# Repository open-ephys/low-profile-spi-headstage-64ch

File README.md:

# Low-profile SPI Headstage with 64 ephys channels

## Accelerometer orientation

## Licensing

The designs, documentation, and photos available in this repository are free: you can redistribute it and/or modify it under the terms of the used license.
Check file named LICENSE.

Copyright Filipe Carvalho and Jonathan Newman 2020-2022

<br />This work is licensed under a <a rel="license" href="http://creativecommons.org/licenses/by-nc-sa/3.0/igo/">Creative Commons Attribution-NonCommercial-ShareAlike 3.0 IGO License</a>.

If your are interested in obtaining a license to sell this device, please contact info@open-ephys.org

[1]: https://docs.google.com/spreadsheets/d/1aobmmEzBDethzIlrm1eg0eYkBqlyX3s9WbA9KgRwVQI/edit?usp=sharing

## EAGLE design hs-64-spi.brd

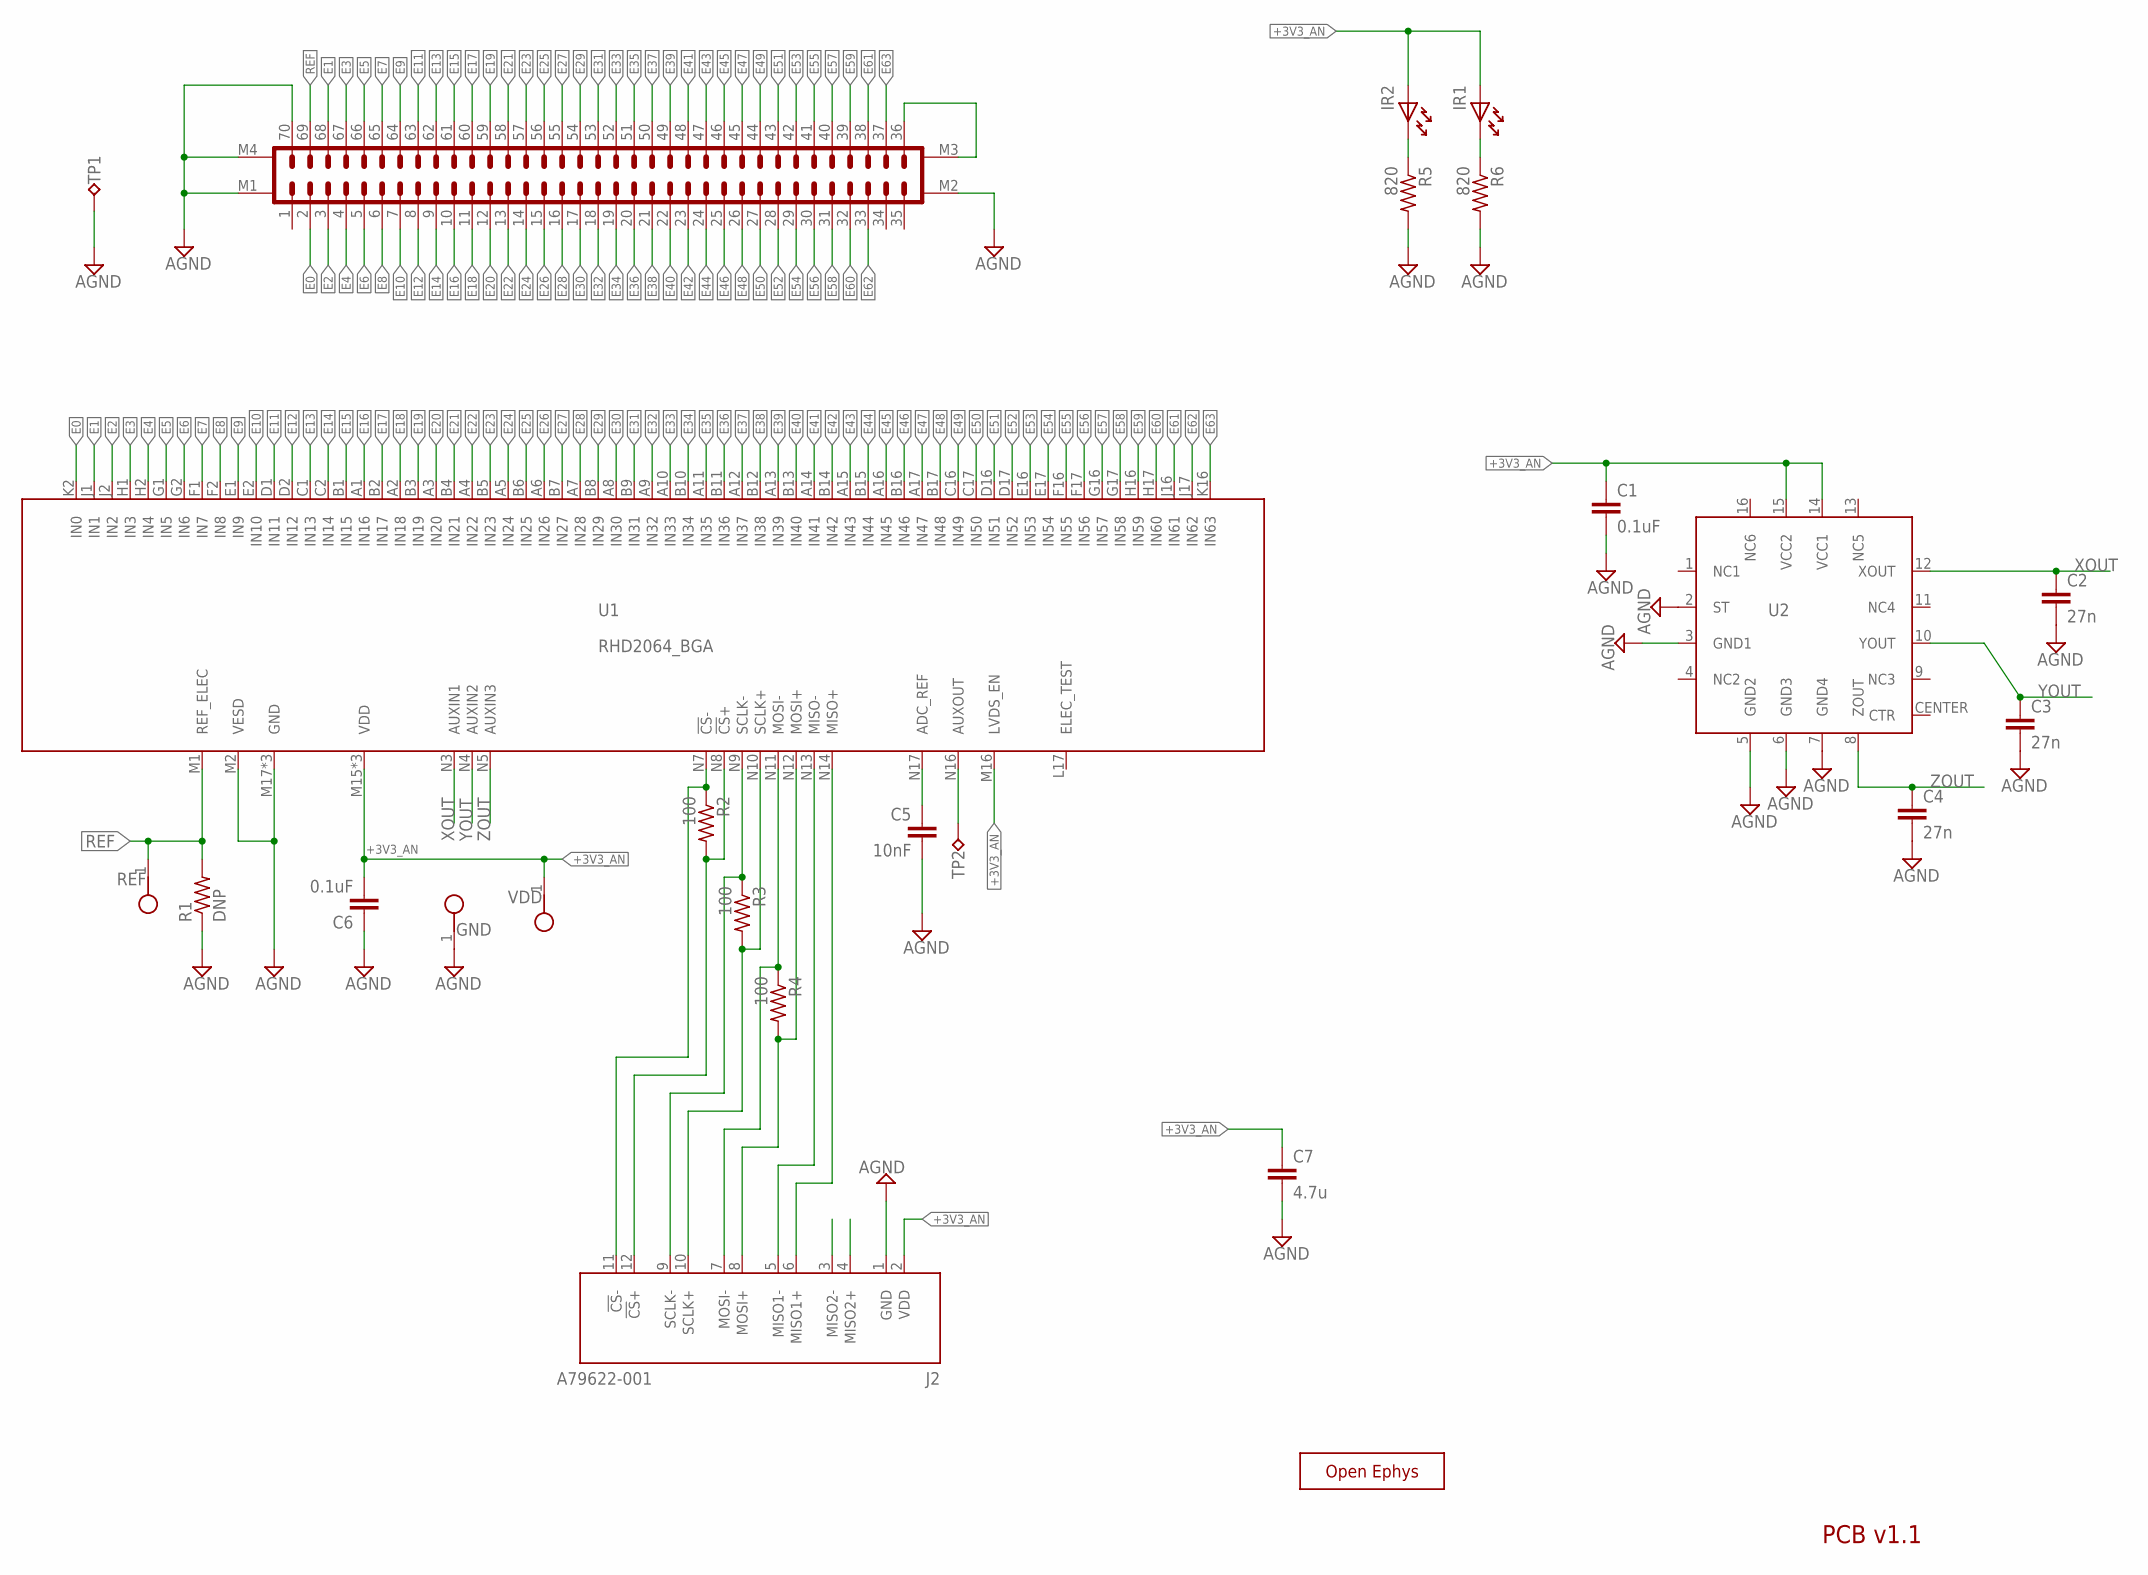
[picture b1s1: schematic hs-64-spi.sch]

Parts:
C1: 0.1uF; 0402
C2, C3, C4: 27n; 0402
C5: 10nF; 0402T; PARTNO GRM033R71E103KE14D
C6: 0.1uF; 0402T
C7: 4.7u; 0402
GND: TESTPOINT_SMALL
IR1, IR2: LEDHAND; LED_HAND
J1: DF40C-70DP-0.4V(51); DF40-70HEAD-LESS-SILK
J2: A79622-001
R1: DNP; 0603
R2, R3, R4: 100; 0402
R5, R6: 820; 0402
REF: TESTPOINT_SMALL
TP1, TP2: VCC; TP07R
U1: RHD2064_BGA; BGA104_0.5MM
U2: ADXL335_IDAX
VDD: TESTPOINT_SMALL
X: OE-LOGO_3.5X2.5; OE-LOGO-3.5X2.5

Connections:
+3V3_AN: C1.1, C6.2, C7.1, IR1.A, IR2.A, J2.2 (VDD), U1.M15 (VDD), U1.M16 (LVDS_EN), U1.N2 (VDD), U1.N15 (VDD), U2.14 (VCC1), U2.15 (VCC2), VDD.1
AGND: C1.2, C2.2, C3.2, C4.2, C5.2, C6.1, C7.2, GND.1, J1.70, J1.M1, J1.M2, J1.M4, J2.1 (GND), R1.1, R5.2, R6.2, TP1.TP, U1.M2 (VESD), U1.M17 (GND), U1.N1 (GND), U1.N6 (GND), U2.2 (ST), U2.3 (GND1), U2.5 (GND2), U2.6 (GND3), U2.7 (GND4)
E0: J1.2, U1.K2 (IN0)
E1: J1.68, U1.J1 (IN1)
E2: J1.3, U1.J2 (IN2)
E3: J1.67, U1.H1 (IN3)
E4: J1.4, U1.H2 (IN4)
E5: J1.66, U1.G1 (IN5)
E6: J1.5, U1.G2 (IN6)
E7: J1.65, U1.F1 (IN7)
E8: J1.6, U1.F2 (IN8)
E9: J1.64, U1.E1 (IN9)
E10: J1.7, U1.E2 (IN10)
E11: J1.63, U1.D1 (IN11)
E12: J1.8, U1.D2 (IN12)
E13: J1.62, U1.C1 (IN13)
E14: J1.9, U1.C2 (IN14)
E15: J1.61, U1.B1 (IN15)
E16: J1.10, U1.A1 (IN16)
E17: J1.60, U1.B2 (IN17)
E18: J1.11, U1.A2 (IN18)
E19: J1.59, U1.B3 (IN19)
E20: J1.12, U1.A3 (IN20)
E21: J1.58, U1.B4 (IN21)
E22: J1.13, U1.A4 (IN22)
E23: J1.57, U1.B5 (IN23)
E24: J1.14, U1.A5 (IN24)
E25: J1.56, U1.B6 (IN25)
E26: J1.15, U1.A6 (IN26)
E27: J1.55, U1.B7 (IN27)
E28: J1.16, U1.A7 (IN28)
E29: J1.54, U1.B8 (IN29)
E30: J1.17, U1.A8 (IN30)
E31: J1.53, U1.B9 (IN31)
E32: J1.18, U1.A9 (IN32)
E33: J1.52, U1.A10 (IN33)
E34: J1.19, U1.B10 (IN34)
E35: J1.51, U1.A11 (IN35)
E36: J1.20, U1.B11 (IN36)
E37: J1.50, U1.A12 (IN37)
E38: J1.21, U1.B12 (IN38)
E39: J1.49, U1.A13 (IN39)
E40: J1.22, U1.B13 (IN40)
E41: J1.48, U1.A14 (IN41)
E42: J1.23, U1.B14 (IN42)
E43: J1.47, U1.A15 (IN43)
E44: J1.24, U1.B15 (IN44)
E45: J1.46, U1.A16 (IN45)
E46: J1.25, U1.B16 (IN46)
E47: J1.45, U1.A17 (IN47)
E48: J1.26, U1.B17 (IN48)
E49: J1.44, U1.C16 (IN49)
E50: J1.27, U1.C17 (IN50)
E51: J1.43, U1.D16 (IN51)
E52: J1.28, U1.D17 (IN52)
E53: J1.42, U1.E16 (IN53)
E54: J1.29, U1.E17 (IN54)
E55: J1.41, U1.F16 (IN55)
E56: J1.30, U1.F17 (IN56)
E57: J1.40, U1.G16 (IN57)
E58: J1.31, U1.G17 (IN58)
E59: J1.39, U1.H16 (IN59)
E60: J1.32, U1.H17 (IN60)
E61: J1.38, U1.J16 (IN61)
E62: J1.33, U1.J17 (IN62)
E63: J1.37, U1.K16 (IN63)
unnamed: IR2.K, R5.1
unnamed: IR1.K, R6.1
unnamed: C5.1, U1.N17 (ADC_REF)
unnamed: TP2.TP, U1.N16 (AUXOUT)
REF: J1.69, R1.2, REF.1, U1.M1 (REF_ELEC)
RHD_CLK_N: J2.9 (SCLK-), R3.1, U1.N9 (SCLK-)
RHD_CLK_P: J2.10 (SCLK+), R3.2, U1.N10 (SCLK+)
RHD_CS_N: J2.11 (!CS!-), R2.1, U1.N7 (!CS!-)
RHD_CS_P: J2.12 (!CS!+), R2.2, U1.N8 (!CS!+)
RHD_MISO_N: J2.5 (MISO1-), U1.N13 (MISO-)
RHD_MISO_P: J2.6 (MISO1+), U1.N14 (MISO+)
RHD_MOSI_N: J2.7 (MOSI-), R4.1, U1.N11 (MOSI-)
RHD_MOSI_P: J2.8 (MOSI+), R4.2, U1.N12 (MOSI+)
VCOAX: J1.36, J1.M3
XOUT: C2.1, U1.N3 (AUXIN1), U2.12 (XOUT)
YOUT: C3.1, U1.N4 (AUXIN2), U2.10 (YOUT)
ZOUT: C4.1, U1.N5 (AUXIN3), U2.8 (ZOUT)

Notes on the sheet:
PCB v1.1

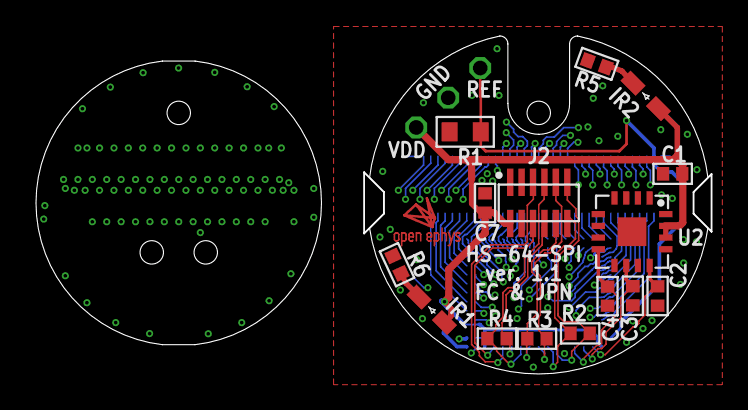
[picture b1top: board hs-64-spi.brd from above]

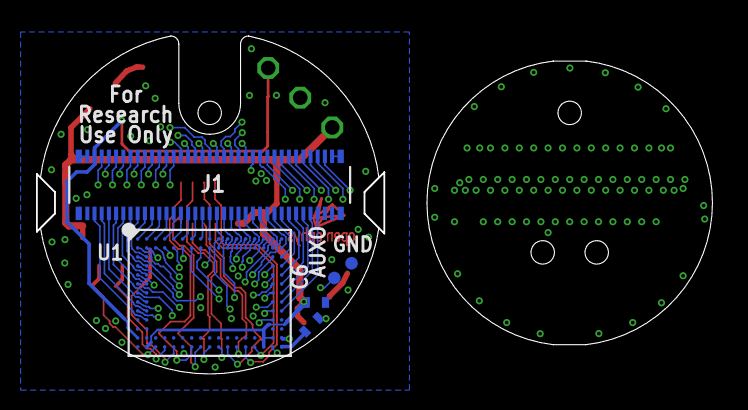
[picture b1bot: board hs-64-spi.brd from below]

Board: 4 copper layers, 37.5 x 18.7 mm, 25 parts (6 on the bottom side), 83 nets.

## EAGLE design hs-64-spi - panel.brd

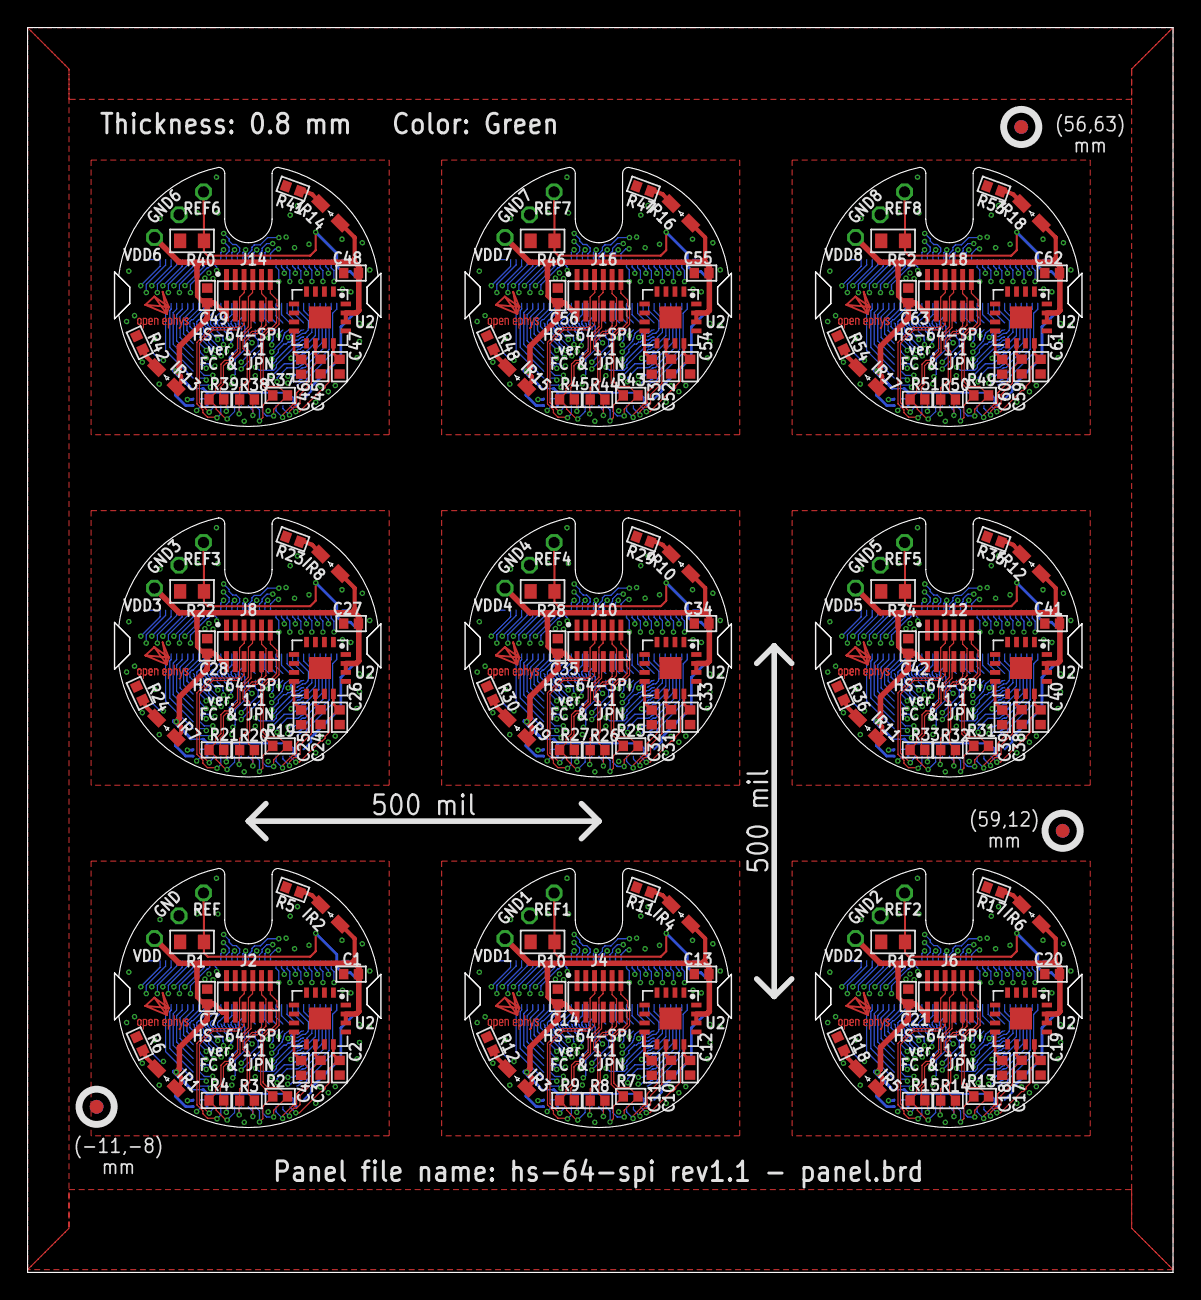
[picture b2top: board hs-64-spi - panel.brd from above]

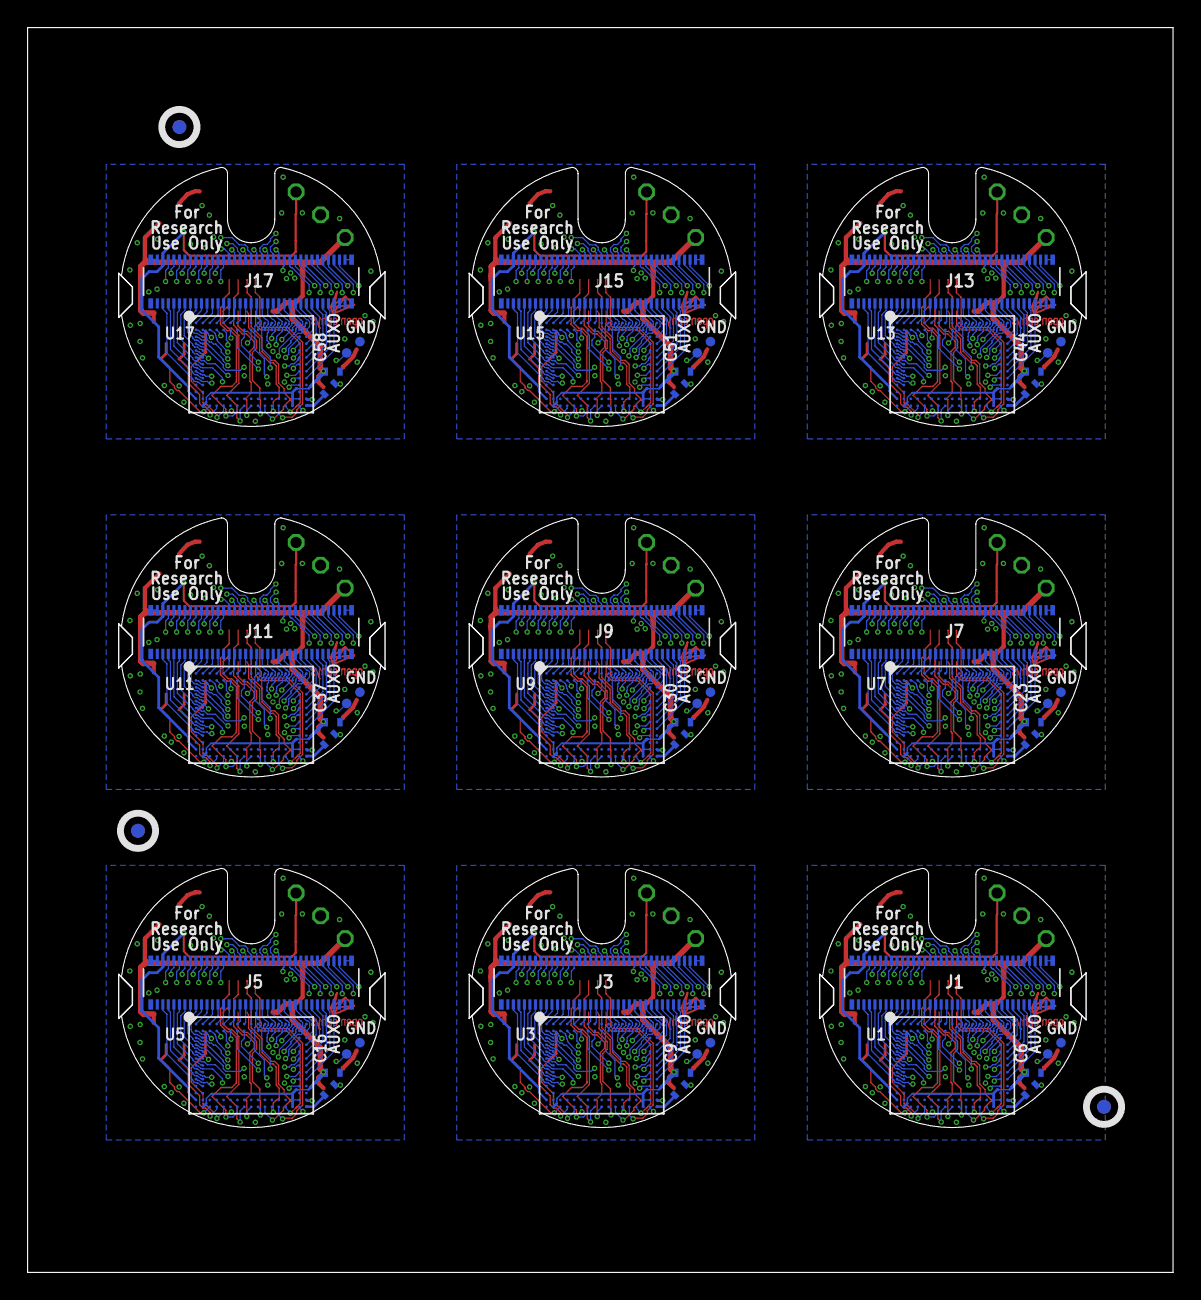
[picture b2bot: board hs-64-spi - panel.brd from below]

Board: 4 copper layers, 82.9 x 90.1 mm, 231 parts (57 on the bottom side), 747 nets.

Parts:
C1, C13, C20, C27, C34, C41, C48, C55, C62: 0.1uF; 0402
C2, C3, C4, C10, C11, C12, C17, C18, C19, C24, C25, C26, C31, C32, C33, C38, C39, C40, C45, C46, C47, C52, C53, C54, C59, C60, C61: 27n; 0402
C5, C8, C15, C22, C29, C36, C43, C50, C57: 10nF; 0402T
C6, C9, C16, C23, C30, C37, C44, C51, C58: 0.1uF; 0402T
C7, C14, C21, C28, C35, C42, C49, C56, C63: 1u; 0402
E$1, E$2, E$3, E$4, E$5, E$6: FIDUCIAL
GND, GND1, GND2, GND3, GND4, GND5, GND6, GND7, GND8: TESTPOINT_SMALL
IR1, IR2, IR3, IR4, IR5, IR6, IR7, IR8, IR9, IR10, IR11, IR12, IR13, IR14, IR15, IR16, IR17, IR18: LED_HAND
J1, J3, J5, J7, J9, J11, J13, J15, J17: DF40C-70DP-0.4V(51); DF40-70HEAD-LESS-SILK
J2, J4, J6, J8, J10, J12, J14, J16, J18: A79622-001
R1, R10, R16, R22, R28, R34, R40, R46, R52: DNP; 0603
R2, R3, R4, R7, R8, R9, R13, R14, R15, R19, R20, R21, R25, R26, R27, R31, R32, R33, R37, R38, R39, R43, R44, R45, R49, R50, R51: 100; 0402
R5, R6, R11, R12, R17, R18, R23, R24, R29, R30, R35, R36, R41, R42, R47, R48, R53, R54: 820; 0402
REF, REF1, REF2, REF3, REF4, REF5, REF6, REF7, REF8: TESTPOINT_SMALL
TP1, TP2, TP3, TP4, TP5, TP6, TP7, TP8, TP9, TP10, TP11, TP12, TP13, TP14, TP15, TP16, TP17, TP18: VCC; TP07R
U1, U3, U5, U7, U9, U11, U13, U15, U17: RHD2064_BGA; BGA104_0.5MM
U2, U4, U6, U8, U10, U12, U14, U16, U18: ADXL335_IDAX
VDD, VDD1, VDD2, VDD3, VDD4, VDD5, VDD6, VDD7, VDD8: TESTPOINT_SMALL
X, X1, X2, X3, X4, X5, X6, X7, X8: OE-LOGO_3.5X2.5; OE-LOGO-3.5X2.5

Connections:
+3V3_AN: C1.1, C6.2, C7.1, IR1.A, IR2.A, J2.2, U1.M15, U1.M16, U1.N2, U1.N15, U2.14, U2.15, VDD.1
+3V3_AN1: C9.2, C13.1, C14.1, IR3.A, IR4.A, J4.2, U3.M15, U3.M16, U3.N2, U3.N15, U4.14, U4.15, VDD1.1
+3V3_AN2: C16.2, C20.1, C21.1, IR5.A, IR6.A, J6.2, U5.M15, U5.M16, U5.N2, U5.N15, U6.14, U6.15, VDD2.1
+3V3_AN3: C23.2, C27.1, C28.1, IR7.A, IR8.A, J8.2, U7.M15, U7.M16, U7.N2, U7.N15, U8.14, U8.15, VDD3.1
+3V3_AN4: C30.2, C34.1, C35.1, IR9.A, IR10.A, J10.2, U9.M15, U9.M16, U9.N2, U9.N15, U10.14, U10.15, VDD4.1
+3V3_AN5: C37.2, C41.1, C42.1, IR11.A, IR12.A, J12.2, U11.M15, U11.M16, U11.N2, U11.N15, U12.14, U12.15, VDD5.1
+3V3_AN6: C44.2, C48.1, C49.1, IR13.A, IR14.A, J14.2, U13.M15, U13.M16, U13.N2, U13.N15, U14.14, U14.15, VDD6.1
+3V3_AN7: C51.2, C55.1, C56.1, IR15.A, IR16.A, J16.2, U15.M15, U15.M16, U15.N2, U15.N15, U16.14, U16.15, VDD7.1
+3V3_AN8: C58.2, C62.1, C63.1, IR17.A, IR18.A, J18.2, U17.M15, U17.M16, U17.N2, U17.N15, U18.14, U18.15, VDD8.1
AGND6: C1.2, C2.2, C3.2, C4.2, C5.2, C6.1, C7.2, GND.1, J1.70, J1.M1, J1.M2, J1.M4, J2.1, R1.1, R5.2, R6.2, TP1.TP, U1.M2, U1.M17, U1.N1, U1.N6, U2.2, U2.3, U2.5, U2.6, U2.7
AGND7: C8.2, C9.1, C10.2, C11.2, C12.2, C13.2, C14.2, GND1.1, J3.70, J3.M1, J3.M2, J3.M4, J4.1, R10.1, R11.2, R12.2, TP4.TP, U3.M2, U3.M17, U3.N1, U3.N6, U4.2, U4.3, U4.5, U4.6, U4.7
AGND8: C15.2, C16.1, C17.2, C18.2, C19.2, C20.2, C21.2, GND2.1, J5.70, J5.M1, J5.M2, J5.M4, J6.1, R16.1, R17.2, R18.2, TP6.TP, U5.M2, U5.M17, U5.N1, U5.N6, U6.2, U6.3, U6.5, U6.6, U6.7
AGND9: C22.2, C23.1, C24.2, C25.2, C26.2, C27.2, C28.2, GND3.1, J7.70, J7.M1, J7.M2, J7.M4, J8.1, R22.1, R23.2, R24.2, TP8.TP, U7.M2, U7.M17, U7.N1, U7.N6, U8.2, U8.3, U8.5, U8.6, U8.7
AGND10: C29.2, C30.1, C31.2, C32.2, C33.2, C34.2, C35.2, GND4.1, J9.70, J9.M1, J9.M2, J9.M4, J10.1, R28.1, R29.2, R30.2, TP10.TP, U9.M2, U9.M17, U9.N1, U9.N6, U10.2, U10.3, U10.5, U10.6, U10.7
AGND11: C36.2, C37.1, C38.2, C39.2, C40.2, C41.2, C42.2, GND5.1, J11.70, J11.M1, J11.M2, J11.M4, J12.1, R34.1, R35.2, R36.2, TP12.TP, U11.M2, U11.M17, U11.N1, U11.N6, U12.2, U12.3, U12.5, U12.6, U12.7
AGND12: C43.2, C44.1, C45.2, C46.2, C47.2, C48.2, C49.2, GND6.1, J13.70, J13.M1, J13.M2, J13.M4, J14.1, R40.1, R41.2, R42.2, TP14.TP, U13.M2, U13.M17, U13.N1, U13.N6, U14.2, U14.3, U14.5, U14.6, U14.7
AGND13: C50.2, C51.1, C52.2, C53.2, C54.2, C55.2, C56.2, GND7.1, J15.70, J15.M1, J15.M2, J15.M4, J16.1, R46.1, R47.2, R48.2, TP16.TP, U15.M2, U15.M17, U15.N1, U15.N6, U16.2, U16.3, U16.5, U16.6, U16.7
AGND14: C57.2, C58.1, C59.2, C60.2, C61.2, C62.2, C63.2, GND8.1, J17.70, J17.M1, J17.M2, J17.M4, J18.1, R52.1, R53.2, R54.2, TP18.TP, U17.M2, U17.M17, U17.N1, U17.N6, U18.2, U18.3, U18.5, U18.6, U18.7
E0: J1.2, U1.K2
E1: J1.68, U1.J1
E2: J1.3, U1.J2
E3: J1.67, U1.H1
E4: J1.4, U1.H2
E5: J1.66, U1.G1
E6: J1.5, U1.G2
E7: J1.65, U1.F1
E8: J1.6, U1.F2
E9: J1.64, U1.E1
E10: J1.7, U1.E2
E11: J1.63, U1.D1
E12: J1.8, U1.D2
E13: J1.62, U1.C1
E14: J1.9, U1.C2
E15: J1.61, U1.B1
E16: J1.10, U1.A1
E17: J1.60, U1.B2
E18: J1.11, U1.A2
E19: J1.59, U1.B3
E20: J1.12, U1.A3
E21: J1.58, U1.B4
E22: J1.13, U1.A4
E23: J1.57, U1.B5
E24: J1.14, U1.A5
E25: J1.56, U1.B6
E26: J1.15, U1.A6
E27: J1.55, U1.B7
E28: J1.16, U1.A7
E29: J1.54, U1.B8
E30: J1.17, U1.A8
E31: J1.53, U1.B9
E32: J1.18, U1.A9
E33: J1.52, U1.A10
E34: J1.19, U1.B10
E35: J1.51, U1.A11
E36: J1.20, U1.B11
E37: J1.50, U1.A12
E38: J1.21, U1.B12
E39: J1.49, U1.A13
E40: J1.22, U1.B13
E41: J1.48, U1.A14
E42: J1.23, U1.B14
E43: J1.47, U1.A15
E44: J1.24, U1.B15
E45: J1.46, U1.A16
E46: J1.25, U1.B16
E47: J1.45, U1.A17
E48: J1.26, U1.B17
E49: J1.44, U1.C16
E50: J1.27, U1.C17
E51: J1.43, U1.D16
E52: J1.28, U1.D17
E53: J1.42, U1.E16
E54: J1.29, U1.E17
E55: J1.41, U1.F16
E56: J1.30, U1.F17
E57: J1.40, U1.G16
E58: J1.31, U1.G17
E59: J1.39, U1.H16
E60: J1.32, U1.H17
E61: J1.38, U1.J16
E62: J1.33, U1.J17
E63: J1.37, U1.K16
E64: J3.17, U3.A8
E65: J3.54, U3.B8
E66: J3.16, U3.A7
E67: J3.55, U3.B7
E68: J3.15, U3.A6
E69: J3.56, U3.B6
E70: J3.14, U3.A5
E71: J3.57, U3.B5
E72: J3.13, U3.A4
E73: J3.58, U3.B4
E74: J3.12, U3.A3
E75: J3.59, U3.B3
E76: J3.11, U3.A2
E77: J3.60, U3.B2
E78: J3.10, U3.A1
E79: J3.61, U3.B1
E80: J3.9, U3.C2
E81: J3.62, U3.C1
E82: J3.8, U3.D2
E83: J3.63, U3.D1
E84: J3.7, U3.E2
E85: J3.64, U3.E1
E86: J3.6, U3.F2
E87: J3.65, U3.F1
E88: J3.5, U3.G2
E89: J3.66, U3.G1
E90: J3.4, U3.H2
E91: J3.67, U3.H1
E92: J3.3, U3.J2
E93: J3.68, U3.J1
E94: J3.2, U3.K2
E95: J3.53, U3.B9
E96: J3.52, U3.A10
E97: J3.19, U3.B10
E98: J3.51, U3.A11
E99: J3.20, U3.B11
E100: J3.50, U3.A12
E101: J3.21, U3.B12
E102: J3.49, U3.A13
E103: J3.22, U3.B13
E104: J3.48, U3.A14
E105: J3.23, U3.B14
E106: J3.47, U3.A15
E107: J3.24, U3.B15
E108: J3.46, U3.A16
E109: J3.25, U3.B16
E110: J3.45, U3.A17
E111: J3.26, U3.B17
E112: J3.44, U3.C16
E113: J3.27, U3.C17
E114: J3.43, U3.D16
E115: J3.28, U3.D17
E116: J3.42, U3.E16
E117: J3.29, U3.E17
E118: J3.41, U3.F16
E119: J3.30, U3.F17
E120: J3.40, U3.G16
E121: J3.31, U3.G17
E122: J3.39, U3.H16
E123: J3.32, U3.H17
E124: J3.38, U3.J16
E125: J3.33, U3.J17
E126: J3.37, U3.K16
E127: J3.18, U3.A9
E128: J5.17, U5.A8
E129: J5.54, U5.B8
E130: J5.16, U5.A7
E131: J5.55, U5.B7
E132: J5.15, U5.A6
E133: J5.56, U5.B6
E134: J5.14, U5.A5
E135: J5.57, U5.B5
E136: J5.13, U5.A4
E137: J5.58, U5.B4
E138: J5.12, U5.A3
E139: J5.59, U5.B3
E140: J5.11, U5.A2
E141: J5.60, U5.B2
E142: J5.10, U5.A1
E143: J5.61, U5.B1
E144: J5.9, U5.C2
E145: J5.62, U5.C1
E146: J5.8, U5.D2
E147: J5.63, U5.D1
E148: J5.7, U5.E2
E149: J5.64, U5.E1
E150: J5.6, U5.F2
E151: J5.65, U5.F1
E152: J5.5, U5.G2
E153: J5.66, U5.G1
E154: J5.4, U5.H2
E155: J5.67, U5.H1
E156: J5.3, U5.J2
E157: J5.68, U5.J1
E158: J5.2, U5.K2
E159: J5.53, U5.B9
E160: J5.52, U5.A10
E161: J5.19, U5.B10
E162: J5.51, U5.A11
E163: J5.20, U5.B11
E164: J5.50, U5.A12
E165: J5.21, U5.B12
E166: J5.49, U5.A13
E167: J5.22, U5.B13
E168: J5.48, U5.A14
E169: J5.23, U5.B14
E170: J5.47, U5.A15
E171: J5.24, U5.B15
E172: J5.46, U5.A16
E173: J5.25, U5.B16
E174: J5.45, U5.A17
E175: J5.26, U5.B17
E176: J5.44, U5.C16
E177: J5.27, U5.C17
E178: J5.43, U5.D16
E179: J5.28, U5.D17
E180: J5.42, U5.E16
E181: J5.29, U5.E17
E182: J5.41, U5.F16
E183: J5.30, U5.F17
E184: J5.40, U5.G16
E185: J5.31, U5.G17
E186: J5.39, U5.H16
E187: J5.32, U5.H17
E188: J5.38, U5.J16
E189: J5.33, U5.J17
E190: J5.37, U5.K16
E191: J5.18, U5.A9
E192: J7.17, U7.A8
E193: J7.54, U7.B8
E194: J7.16, U7.A7
E195: J7.55, U7.B7
E196: J7.15, U7.A6
E197: J7.56, U7.B6
E198: J7.14, U7.A5
E199: J7.57, U7.B5
E200: J7.13, U7.A4
E201: J7.58, U7.B4
E202: J7.12, U7.A3
E203: J7.59, U7.B3
E204: J7.11, U7.A2
E205: J7.60, U7.B2
E206: J7.10, U7.A1
E207: J7.61, U7.B1
E208: J7.9, U7.C2
E209: J7.62, U7.C1
E210: J7.8, U7.D2
E211: J7.63, U7.D1
E212: J7.7, U7.E2
E213: J7.64, U7.E1
E214: J7.6, U7.F2
E215: J7.65, U7.F1
E216: J7.5, U7.G2
E217: J7.66, U7.G1
E218: J7.4, U7.H2
E219: J7.67, U7.H1
E220: J7.3, U7.J2
E221: J7.68, U7.J1
E222: J7.2, U7.K2
E223: J7.53, U7.B9
E224: J7.52, U7.A10
E225: J7.19, U7.B10
E226: J7.51, U7.A11
E227: J7.20, U7.B11
E228: J7.50, U7.A12
E229: J7.21, U7.B12
E230: J7.49, U7.A13
E231: J7.22, U7.B13
E232: J7.48, U7.A14
E233: J7.23, U7.B14
E234: J7.47, U7.A15
E235: J7.24, U7.B15
E236: J7.46, U7.A16
E237: J7.25, U7.B16
E238: J7.45, U7.A17
E239: J7.26, U7.B17
E240: J7.44, U7.C16
E241: J7.27, U7.C17
E242: J7.43, U7.D16
E243: J7.28, U7.D17
E244: J7.42, U7.E16
E245: J7.29, U7.E17
E246: J7.41, U7.F16
E247: J7.30, U7.F17
E248: J7.40, U7.G16
E249: J7.31, U7.G17
E250: J7.39, U7.H16
E251: J7.32, U7.H17
E252: J7.38, U7.J16
E253: J7.33, U7.J17
E254: J7.37, U7.K16
E255: J7.18, U7.A9
E256: J9.17, U9.A8
E257: J9.54, U9.B8
E258: J9.16, U9.A7
E259: J9.55, U9.B7
E260: J9.15, U9.A6
E261: J9.56, U9.B6
E262: J9.14, U9.A5
E263: J9.57, U9.B5
E264: J9.13, U9.A4
E265: J9.58, U9.B4
E266: J9.12, U9.A3
E267: J9.59, U9.B3
E268: J9.11, U9.A2
E269: J9.60, U9.B2
E270: J9.10, U9.A1
E271: J9.61, U9.B1
E272: J9.9, U9.C2
E273: J9.62, U9.C1
E274: J9.8, U9.D2
E275: J9.63, U9.D1
E276: J9.7, U9.E2
E277: J9.64, U9.E1
E278: J9.6, U9.F2
E279: J9.65, U9.F1
E280: J9.5, U9.G2
E281: J9.66, U9.G1
E282: J9.4, U9.H2
E283: J9.67, U9.H1
E284: J9.3, U9.J2
E285: J9.68, U9.J1
E286: J9.2, U9.K2
E287: J9.53, U9.B9
E288: J9.52, U9.A10
E289: J9.19, U9.B10
E290: J9.51, U9.A11
E291: J9.20, U9.B11
E292: J9.50, U9.A12
E293: J9.21, U9.B12
E294: J9.49, U9.A13
E295: J9.22, U9.B13
E296: J9.48, U9.A14
E297: J9.23, U9.B14
E298: J9.47, U9.A15
E299: J9.24, U9.B15
E300: J9.46, U9.A16
E301: J9.25, U9.B16
E302: J9.45, U9.A17
E303: J9.26, U9.B17
E304: J9.44, U9.C16
E305: J9.27, U9.C17
E306: J9.43, U9.D16
E307: J9.28, U9.D17
E308: J9.42, U9.E16
E309: J9.29, U9.E17
E310: J9.41, U9.F16
E311: J9.30, U9.F17
E312: J9.40, U9.G16
E313: J9.31, U9.G17
E314: J9.39, U9.H16
E315: J9.32, U9.H17
E316: J9.38, U9.J16
E317: J9.33, U9.J17
E318: J9.37, U9.K16
E319: J9.18, U9.A9
E320: J11.17, U11.A8
E321: J11.54, U11.B8
E322: J11.16, U11.A7
E323: J11.55, U11.B7
E324: J11.15, U11.A6
E325: J11.56, U11.B6
E326: J11.14, U11.A5
E327: J11.57, U11.B5
E328: J11.13, U11.A4
E329: J11.58, U11.B4
E330: J11.12, U11.A3
E331: J11.59, U11.B3
E332: J11.11, U11.A2
E333: J11.60, U11.B2
E334: J11.10, U11.A1
E335: J11.61, U11.B1
E336: J11.9, U11.C2
E337: J11.62, U11.C1
E338: J11.8, U11.D2
E339: J11.63, U11.D1
E340: J11.7, U11.E2
E341: J11.64, U11.E1
E342: J11.6, U11.F2
E343: J11.65, U11.F1
E344: J11.5, U11.G2
E345: J11.66, U11.G1
E346: J11.4, U11.H2
E347: J11.67, U11.H1
E348: J11.3, U11.J2
E349: J11.68, U11.J1
E350: J11.2, U11.K2
E351: J11.53, U11.B9
E352: J11.52, U11.A10
E353: J11.19, U11.B10
E354: J11.51, U11.A11
E355: J11.20, U11.B11
E356: J11.50, U11.A12
E357: J11.21, U11.B12
E358: J11.49, U11.A13
E359: J11.22, U11.B13
E360: J11.48, U11.A14
E361: J11.23, U11.B14
E362: J11.47, U11.A15
E363: J11.24, U11.B15
E364: J11.46, U11.A16
E365: J11.25, U11.B16
E366: J11.45, U11.A17
E367: J11.26, U11.B17
E368: J11.44, U11.C16
E369: J11.27, U11.C17
E370: J11.43, U11.D16
E371: J11.28, U11.D17
E372: J11.42, U11.E16
E373: J11.29, U11.E17
E374: J11.41, U11.F16
E375: J11.30, U11.F17
E376: J11.40, U11.G16
E377: J11.31, U11.G17
E378: J11.39, U11.H16
E379: J11.32, U11.H17
E380: J11.38, U11.J16
E381: J11.33, U11.J17
E382: J11.37, U11.K16
E383: J11.18, U11.A9
E384: J13.17, U13.A8
E385: J13.54, U13.B8
E386: J13.16, U13.A7
E387: J13.55, U13.B7
E388: J13.15, U13.A6
E389: J13.56, U13.B6
E390: J13.14, U13.A5
E391: J13.57, U13.B5
E392: J13.13, U13.A4
E393: J13.58, U13.B4
E394: J13.12, U13.A3
E395: J13.59, U13.B3
E396: J13.11, U13.A2
E397: J13.60, U13.B2
E398: J13.10, U13.A1
E399: J13.61, U13.B1
E400: J13.9, U13.C2
E401: J13.62, U13.C1
E402: J13.8, U13.D2
E403: J13.63, U13.D1
E404: J13.7, U13.E2
E405: J13.64, U13.E1
E406: J13.6, U13.F2
E407: J13.65, U13.F1
E408: J13.5, U13.G2
E409: J13.66, U13.G1
E410: J13.4, U13.H2
E411: J13.67, U13.H1
E412: J13.3, U13.J2
E413: J13.68, U13.J1
E414: J13.2, U13.K2
E415: J13.53, U13.B9
E416: J13.52, U13.A10
E417: J13.19, U13.B10
E418: J13.51, U13.A11
E419: J13.20, U13.B11
E420: J13.50, U13.A12
E421: J13.21, U13.B12
E422: J13.49, U13.A13
E423: J13.22, U13.B13
E424: J13.48, U13.A14
E425: J13.23, U13.B14
E426: J13.47, U13.A15
E427: J13.24, U13.B15
E428: J13.46, U13.A16
E429: J13.25, U13.B16
E430: J13.45, U13.A17
E431: J13.26, U13.B17
E432: J13.44, U13.C16
E433: J13.27, U13.C17
E434: J13.43, U13.D16
E435: J13.28, U13.D17
E436: J13.42, U13.E16
E437: J13.29, U13.E17
E438: J13.41, U13.F16
E439: J13.30, U13.F17
E440: J13.40, U13.G16
E441: J13.31, U13.G17
E442: J13.39, U13.H16
E443: J13.32, U13.H17
E444: J13.38, U13.J16
E445: J13.33, U13.J17
E446: J13.37, U13.K16
E447: J13.18, U13.A9
E448: J15.17, U15.A8
E449: J15.54, U15.B8
E450: J15.16, U15.A7
E451: J15.55, U15.B7
E452: J15.15, U15.A6
E453: J15.56, U15.B6
E454: J15.14, U15.A5
E455: J15.57, U15.B5
E456: J15.13, U15.A4
E457: J15.58, U15.B4
E458: J15.12, U15.A3
E459: J15.59, U15.B3
E460: J15.11, U15.A2
E461: J15.60, U15.B2
E462: J15.10, U15.A1
E463: J15.61, U15.B1
E464: J15.9, U15.C2
E465: J15.62, U15.C1
E466: J15.8, U15.D2
E467: J15.63, U15.D1
E468: J15.7, U15.E2
E469: J15.64, U15.E1
E470: J15.6, U15.F2
E471: J15.65, U15.F1
E472: J15.5, U15.G2
E473: J15.66, U15.G1
E474: J15.4, U15.H2
E475: J15.67, U15.H1
E476: J15.3, U15.J2
E477: J15.68, U15.J1
E478: J15.2, U15.K2
E479: J15.53, U15.B9
E480: J15.52, U15.A10
E481: J15.19, U15.B10
E482: J15.51, U15.A11
E483: J15.20, U15.B11
E484: J15.50, U15.A12
E485: J15.21, U15.B12
E486: J15.49, U15.A13
E487: J15.22, U15.B13
E488: J15.48, U15.A14
E489: J15.23, U15.B14
E490: J15.47, U15.A15
E491: J15.24, U15.B15
E492: J15.46, U15.A16
E493: J15.25, U15.B16
E494: J15.45, U15.A17
E495: J15.26, U15.B17
E496: J15.44, U15.C16
E497: J15.27, U15.C17
E498: J15.43, U15.D16
E499: J15.28, U15.D17
E500: J15.42, U15.E16
E501: J15.29, U15.E17
E502: J15.41, U15.F16
E503: J15.30, U15.F17
E504: J15.40, U15.G16
E505: J15.31, U15.G17
E506: J15.39, U15.H16
E507: J15.32, U15.H17
E508: J15.38, U15.J16
E509: J15.33, U15.J17
E510: J15.37, U15.K16
E511: J15.18, U15.A9
E512: J17.17, U17.A8
E513: J17.54, U17.B8
E514: J17.16, U17.A7
E515: J17.55, U17.B7
E516: J17.15, U17.A6
E517: J17.56, U17.B6
E518: J17.14, U17.A5
E519: J17.57, U17.B5
E520: J17.13, U17.A4
E521: J17.58, U17.B4
E522: J17.12, U17.A3
E523: J17.59, U17.B3
E524: J17.11, U17.A2
E525: J17.60, U17.B2
E526: J17.10, U17.A1
E527: J17.61, U17.B1
E528: J17.9, U17.C2
E529: J17.62, U17.C1
E530: J17.8, U17.D2
E531: J17.63, U17.D1
E532: J17.7, U17.E2
E533: J17.64, U17.E1
E534: J17.6, U17.F2
E535: J17.65, U17.F1
E536: J17.5, U17.G2
E537: J17.66, U17.G1
E538: J17.4, U17.H2
E539: J17.67, U17.H1
E540: J17.3, U17.J2
E541: J17.68, U17.J1
E542: J17.2, U17.K2
E543: J17.53, U17.B9
E544: J17.52, U17.A10
E545: J17.19, U17.B10
E546: J17.51, U17.A11
E547: J17.20, U17.B11
E548: J17.50, U17.A12
E549: J17.21, U17.B12
E550: J17.49, U17.A13
E551: J17.22, U17.B13
E552: J17.48, U17.A14
E553: J17.23, U17.B14
E554: J17.47, U17.A15
E555: J17.24, U17.B15
E556: J17.46, U17.A16
E557: J17.25, U17.B16
E558: J17.45, U17.A17
E559: J17.26, U17.B17
E560: J17.44, U17.C16
E561: J17.27, U17.C17
E562: J17.43, U17.D16
E563: J17.28, U17.D17
E564: J17.42, U17.E16
E565: J17.29, U17.E17
E566: J17.41, U17.F16
E567: J17.30, U17.F17
E568: J17.40, U17.G16
E569: J17.31, U17.G17
E570: J17.39, U17.H16
E571: J17.32, U17.H17
E572: J17.38, U17.J16
E573: J17.33, U17.J17
E574: J17.37, U17.K16
E575: J17.18, U17.A9
unnamed: IR2.K, R5.1
unnamed: IR1.K, R6.1
unnamed: C8.1, U3.N17
unnamed: TP3.TP, U3.N16
unnamed: IR4.K, R11.1
unnamed: IR3.K, R12.1
unnamed: C15.1, U5.N17
unnamed: TP5.TP, U5.N16
unnamed: IR6.K, R17.1
unnamed: IR5.K, R18.1
unnamed: C22.1, U7.N17
unnamed: TP7.TP, U7.N16
unnamed: IR8.K, R23.1
unnamed: IR7.K, R24.1
unnamed: C29.1, U9.N17
unnamed: TP9.TP, U9.N16
unnamed: IR10.K, R29.1
unnamed: IR9.K, R30.1
unnamed: C36.1, U11.N17
unnamed: TP11.TP, U11.N16
unnamed: IR12.K, R35.1
unnamed: IR11.K, R36.1
unnamed: C43.1, U13.N17
unnamed: C5.1, U1.N17
unnamed: TP13.TP, U13.N16
unnamed: TP2.TP, U1.N16
unnamed: IR14.K, R41.1
unnamed: IR13.K, R42.1
unnamed: C50.1, U15.N17
unnamed: TP15.TP, U15.N16
unnamed: IR16.K, R47.1
unnamed: IR15.K, R48.1
unnamed: C57.1, U17.N17
unnamed: TP17.TP, U17.N16
unnamed: IR18.K, R53.1
unnamed: IR17.K, R54.1
REF: J1.69, R1.2, REF.1, U1.M1
REF1: J3.69, R10.2, REF1.1, U3.M1
REF2: J5.69, R16.2, REF2.1, U5.M1
REF3: J7.69, R22.2, REF3.1, U7.M1
REF4: J9.69, R28.2, REF4.1, U9.M1
REF5: J11.69, R34.2, REF5.1, U11.M1
REF6: J13.69, R40.2, REF6.1, U13.M1
REF7: J15.69, R46.2, REF7.1, U15.M1
REF8: J17.69, R52.2, REF8.1, U17.M1
RHD_CLK_N: J2.9, R3.1, U1.N9
RHD_CLK_N1: J4.9, R8.1, U3.N9
RHD_CLK_N2: J6.9, R14.1, U5.N9
RHD_CLK_N3: J8.9, R20.1, U7.N9
RHD_CLK_N4: J10.9, R26.1, U9.N9
RHD_CLK_N5: J12.9, R32.1, U11.N9
RHD_CLK_N6: J14.9, R38.1, U13.N9
RHD_CLK_N7: J16.9, R44.1, U15.N9
RHD_CLK_N8: J18.9, R50.1, U17.N9
RHD_CLK_P: J2.10, R3.2, U1.N10
RHD_CLK_P1: J4.10, R8.2, U3.N10
RHD_CLK_P2: J6.10, R14.2, U5.N10
RHD_CLK_P3: J8.10, R20.2, U7.N10
RHD_CLK_P4: J10.10, R26.2, U9.N10
RHD_CLK_P5: J12.10, R32.2, U11.N10
RHD_CLK_P6: J14.10, R38.2, U13.N10
RHD_CLK_P7: J16.10, R44.2, U15.N10
RHD_CLK_P8: J18.10, R50.2, U17.N10
RHD_CS_N: J2.11, R2.1, U1.N7
RHD_CS_N1: J4.11, R7.1, U3.N7
RHD_CS_N2: J6.11, R13.1, U5.N7
RHD_CS_N3: J8.11, R19.1, U7.N7
RHD_CS_N4: J10.11, R25.1, U9.N7
RHD_CS_N5: J12.11, R31.1, U11.N7
RHD_CS_N6: J14.11, R37.1, U13.N7
RHD_CS_N7: J16.11, R43.1, U15.N7
RHD_CS_N8: J18.11, R49.1, U17.N7
RHD_CS_P: J2.12, R2.2, U1.N8
RHD_CS_P1: J4.12, R7.2, U3.N8
RHD_CS_P2: J6.12, R13.2, U5.N8
RHD_CS_P3: J8.12, R19.2, U7.N8
RHD_CS_P4: J10.12, R25.2, U9.N8
RHD_CS_P5: J12.12, R31.2, U11.N8
RHD_CS_P6: J14.12, R37.2, U13.N8
RHD_CS_P7: J16.12, R43.2, U15.N8
RHD_CS_P8: J18.12, R49.2, U17.N8
RHD_MISO_N: J2.5, U1.N13
RHD_MISO_N1: J4.5, U3.N13
RHD_MISO_N2: J6.5, U5.N13
RHD_MISO_N3: J8.5, U7.N13
RHD_MISO_N4: J10.5, U9.N13
RHD_MISO_N5: J12.5, U11.N13
RHD_MISO_N6: J14.5, U13.N13
RHD_MISO_N7: J16.5, U15.N13
RHD_MISO_N8: J18.5, U17.N13
RHD_MISO_P: J2.6, U1.N14
RHD_MISO_P1: J4.6, U3.N14
RHD_MISO_P2: J6.6, U5.N14
RHD_MISO_P3: J8.6, U7.N14
RHD_MISO_P4: J10.6, U9.N14
RHD_MISO_P5: J12.6, U11.N14
RHD_MISO_P6: J14.6, U13.N14
RHD_MISO_P7: J16.6, U15.N14
RHD_MISO_P8: J18.6, U17.N14
RHD_MOSI_N: J2.7, R4.1, U1.N11
RHD_MOSI_N1: J4.7, R9.1, U3.N11
RHD_MOSI_N2: J6.7, R15.1, U5.N11
RHD_MOSI_N3: J8.7, R21.1, U7.N11
RHD_MOSI_N4: J10.7, R27.1, U9.N11
RHD_MOSI_N5: J12.7, R33.1, U11.N11
RHD_MOSI_N6: J14.7, R39.1, U13.N11
RHD_MOSI_N7: J16.7, R45.1, U15.N11
RHD_MOSI_N8: J18.7, R51.1, U17.N11
RHD_MOSI_P: J2.8, R4.2, U1.N12
RHD_MOSI_P1: J4.8, R9.2, U3.N12
RHD_MOSI_P2: J6.8, R15.2, U5.N12
RHD_MOSI_P3: J8.8, R21.2, U7.N12
RHD_MOSI_P4: J10.8, R27.2, U9.N12
RHD_MOSI_P5: J12.8, R33.2, U11.N12
RHD_MOSI_P6: J14.8, R39.2, U13.N12
RHD_MOSI_P7: J16.8, R45.2, U15.N12
RHD_MOSI_P8: J18.8, R51.2, U17.N12
VCOAX: J1.36, J1.M3
VCOAX1: J3.36, J3.M3
VCOAX2: J5.36, J5.M3
VCOAX3: J7.36, J7.M3
VCOAX4: J9.36, J9.M3
VCOAX5: J11.36, J11.M3
VCOAX6: J13.36, J13.M3
VCOAX7: J15.36, J15.M3
VCOAX8: J17.36, J17.M3
XOUT: C2.1, U1.N3, U2.12
XOUT1: C12.1, U3.N3, U4.12
XOUT2: C19.1, U5.N3, U6.12
XOUT3: C26.1, U7.N3, U8.12
XOUT4: C33.1, U9.N3, U10.12
XOUT5: C40.1, U11.N3, U12.12
XOUT6: C47.1, U13.N3, U14.12
XOUT7: C54.1, U15.N3, U16.12
XOUT8: C61.1, U17.N3, U18.12
YOUT: C3.1, U1.N4, U2.10
YOUT1: C10.1, U3.N4, U4.10
YOUT2: C17.1, U5.N4, U6.10
YOUT3: C24.1, U7.N4, U8.10
YOUT4: C31.1, U9.N4, U10.10
YOUT5: C38.1, U11.N4, U12.10
YOUT6: C45.1, U13.N4, U14.10
YOUT7: C52.1, U15.N4, U16.10
YOUT8: C59.1, U17.N4, U18.10
ZOUT: C4.1, U1.N5, U2.8
ZOUT1: C11.1, U3.N5, U4.8
ZOUT2: C18.1, U5.N5, U6.8
ZOUT3: C25.1, U7.N5, U8.8
ZOUT4: C32.1, U9.N5, U10.8
ZOUT5: C39.1, U11.N5, U12.8
ZOUT6: C46.1, U13.N5, U14.8
ZOUT7: C53.1, U15.N5, U16.8
ZOUT8: C60.1, U17.N5, U18.8

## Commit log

2020-09-03 Added README and LICENSE.
2020-09-03 Added the PCB design files.
2020-09-03 Added production files.
2020-09-03 Added pictures and .gitignore.
2020-09-04 Minor correction to README.
2022-10-09 Added PCB design files for the new version 1.1.
2022-10-09 Added fiducials on bottom.
2022-10-09 Updated mechanical dimensions.
2022-10-09 Added version label.
2022-11-14 Added drill files.
2023-01-09 Add R1 to assembly.
2023-07-06 added accelerometer orientation
2023-10-07 Corrected C7 value to 4.7uF.
2024-03-20 Updated Hirose (J1) schematic.
2025-02-13 Reorganize gerber files.

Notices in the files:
hs-64-spi.sch:
LICENSE: CERN OHL v1.2
